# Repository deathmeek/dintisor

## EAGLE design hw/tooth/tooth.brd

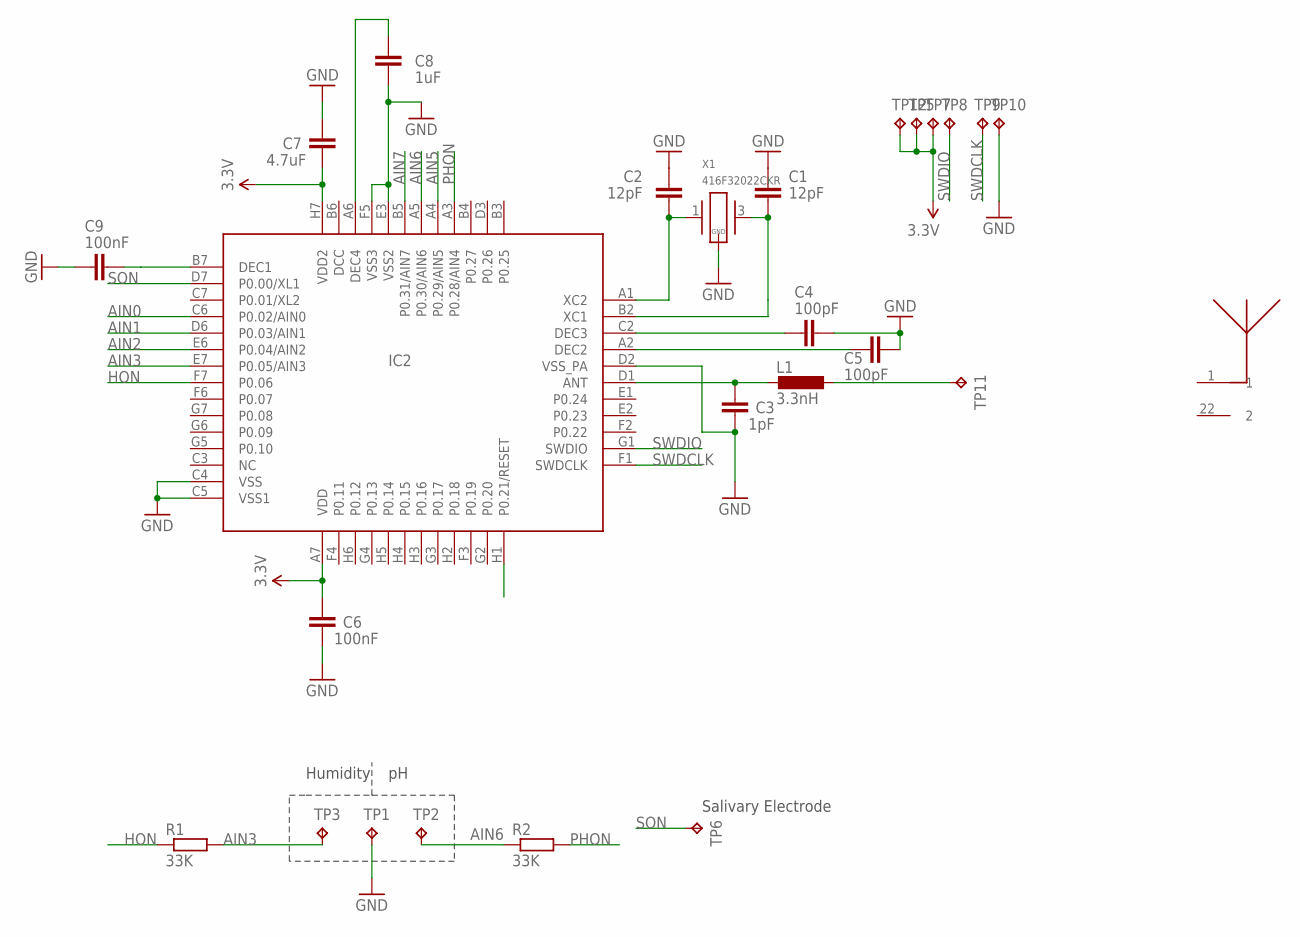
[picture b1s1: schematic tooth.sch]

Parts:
C1, C2: 12pF; C0201
C3: 1pF; C0201
C4, C5: 100pF; C0201
C6, C9: 100nF; C0201
C7: 4.7uF; C0402
C8: 1uF; C0402
IC2: NRF52832; NRF52832_WLCSP
L1: 3.3nH; L0201
R1, R2: 33K; R0201
TP1, TP2, TP3, TP11: TPTP10R; TP10R
TP5, TP6, TP7, TP8, TP9, TP10, TP12: TPTP15R; TP15R
U$1: ACA-102-T
X1: 416F32022CKR; M416

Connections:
3.3V: C6.2, C7.2, IC2.A7 (VDD), IC2.H7 (VDD2), TP5.TP, TP7.TP, TP12.TP
AIN0: IC2.C6 (P0.02/AIN0)
AIN1: IC2.D6 (P0.03/AIN1)
AIN2: IC2.E6 (P0.04/AIN2)
AIN3: IC2.E7 (P0.05/AIN3), R1.2, TP3.TP
AIN5: IC2.A4 (P0.29/AIN5)
AIN6: IC2.A5 (P0.30/AIN6), R2.1, TP2.TP
AIN7: IC2.B5 (P0.31/AIN7)
GND: C1.1, C2.1, C3.2, C4.2, C5.2, C6.1, C7.1, C8.2, C9.2, IC2.C4 (VSS), IC2.C5 (VSS1), IC2.D2 (VSS_PA), IC2.E3 (VSS2), IC2.F5 (VSS3), TP1.TP, TP10.TP, X1.2 (GND), X1.4 (GND)
HON: IC2.F7 (P0.06), R1.1
unnamed: C2.2, IC2.A1 (XC2), X1.1
unnamed: L1.1, TP11.TP
unnamed: C1.2, IC2.B2 (XC1), X1.3 (2)
unnamed: C4.1, IC2.C2 (DEC3)
unnamed: C5.1, IC2.A2 (DEC2)
unnamed: C3.1, IC2.D1 (ANT), L1.2
unnamed: C9.1, IC2.B7 (DEC1)
unnamed: C8.1, IC2.A6 (DEC4)
PHON: IC2.A3 (P0.28/AIN4), R2.2
SON: IC2.D7 (P0.00/XL1), TP6.TP
SWDCLK: IC2.F1 (SWDCLK), TP9.TP
SWDIO: IC2.G1 (SWDIO), TP8.TP

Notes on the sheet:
Humidity
Salivary Electrode

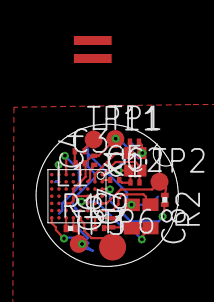
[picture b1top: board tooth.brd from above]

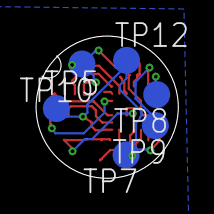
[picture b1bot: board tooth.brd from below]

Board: 2 copper layers, 7.9 x 7.9 mm, 26 parts (6 on the bottom side), 17 nets.

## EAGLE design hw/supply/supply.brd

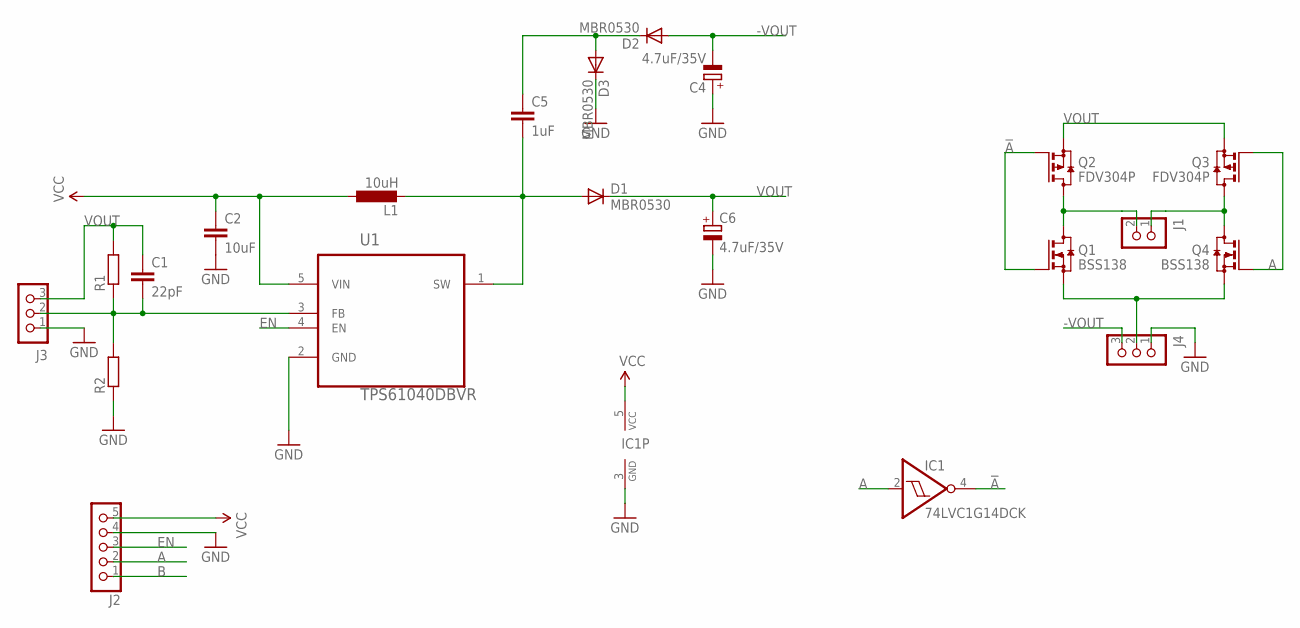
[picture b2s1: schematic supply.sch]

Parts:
C1: 22pF; C0603
C2: 10uF; C0603
C4, C6: 4.7uF/35V; 140CLH-1010
C5: 1uF; C0603
D1, D2, D3: MBR0530; SOD123
IC1: 74LVC1G14DCK; SC70-5
J1: CON_HEADER_1X02-PTH; M1X2
J2: CON_HEADER_1X05-PTH; M1X5
J3, J4: CON_HEADER_1X03-PTH; M1X3
L1: 10uH; L2825P
Q1, Q4: BSS138; SOT23
Q2, Q3: FDV304P; SOT23
R1, R2: R-EU_R0603; R0603
U1: TPS61040DBVR; SOT95P280X145-5N

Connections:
!A: IC1.4 (O), Q1.1 (G), Q2.1 (G)
-VOUT: C4.-, D2.A, J4.3
A: IC1.2 (I), J2.2, Q3.1 (G), Q4.1 (G)
B: J2.1
EN: J2.3, U1.4 (EN)
GND: C2.2, C4.+, C6.-, D3.C, IC1.3 (GND), J2.4, J3.1, J4.1, R2.1, U1.2 (GND)
unnamed: C1.2, J3.2, R1.1, R2.2, U1.3 (FB)
unnamed: C5.2, D1.A, L1.2, U1.1 (SW)
unnamed: J1.2, Q1.3 (D), Q2.3 (D)
unnamed: J1.1, Q3.3 (D), Q4.3 (D)
unnamed: C5.1, D2.C, D3.A
unnamed: J4.2, Q1.2 (S), Q4.2 (S)
VCC: C2.1, IC1.5 (VCC), J2.5, L1.1, U1.5 (VIN)
VOUT: C1.1, C6.+, D1.C, J3.3, Q2.2 (S), Q3.2 (S), R1.2

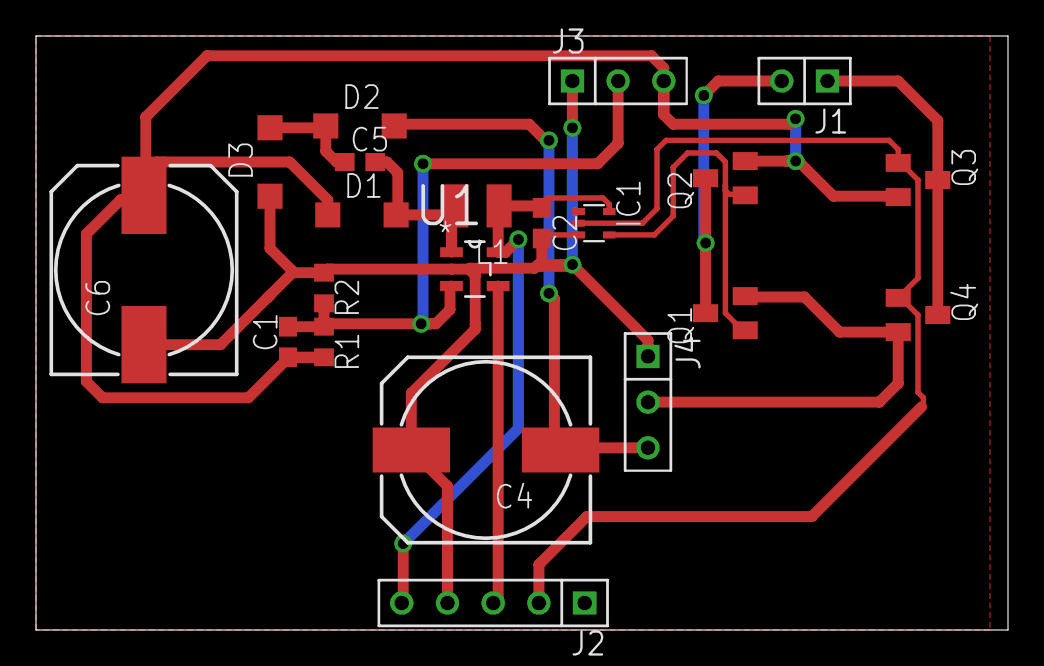
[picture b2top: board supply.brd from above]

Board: 2 copper layers, 54.0 x 33.0 mm, 21 parts (0 on the bottom side), 13 nets.

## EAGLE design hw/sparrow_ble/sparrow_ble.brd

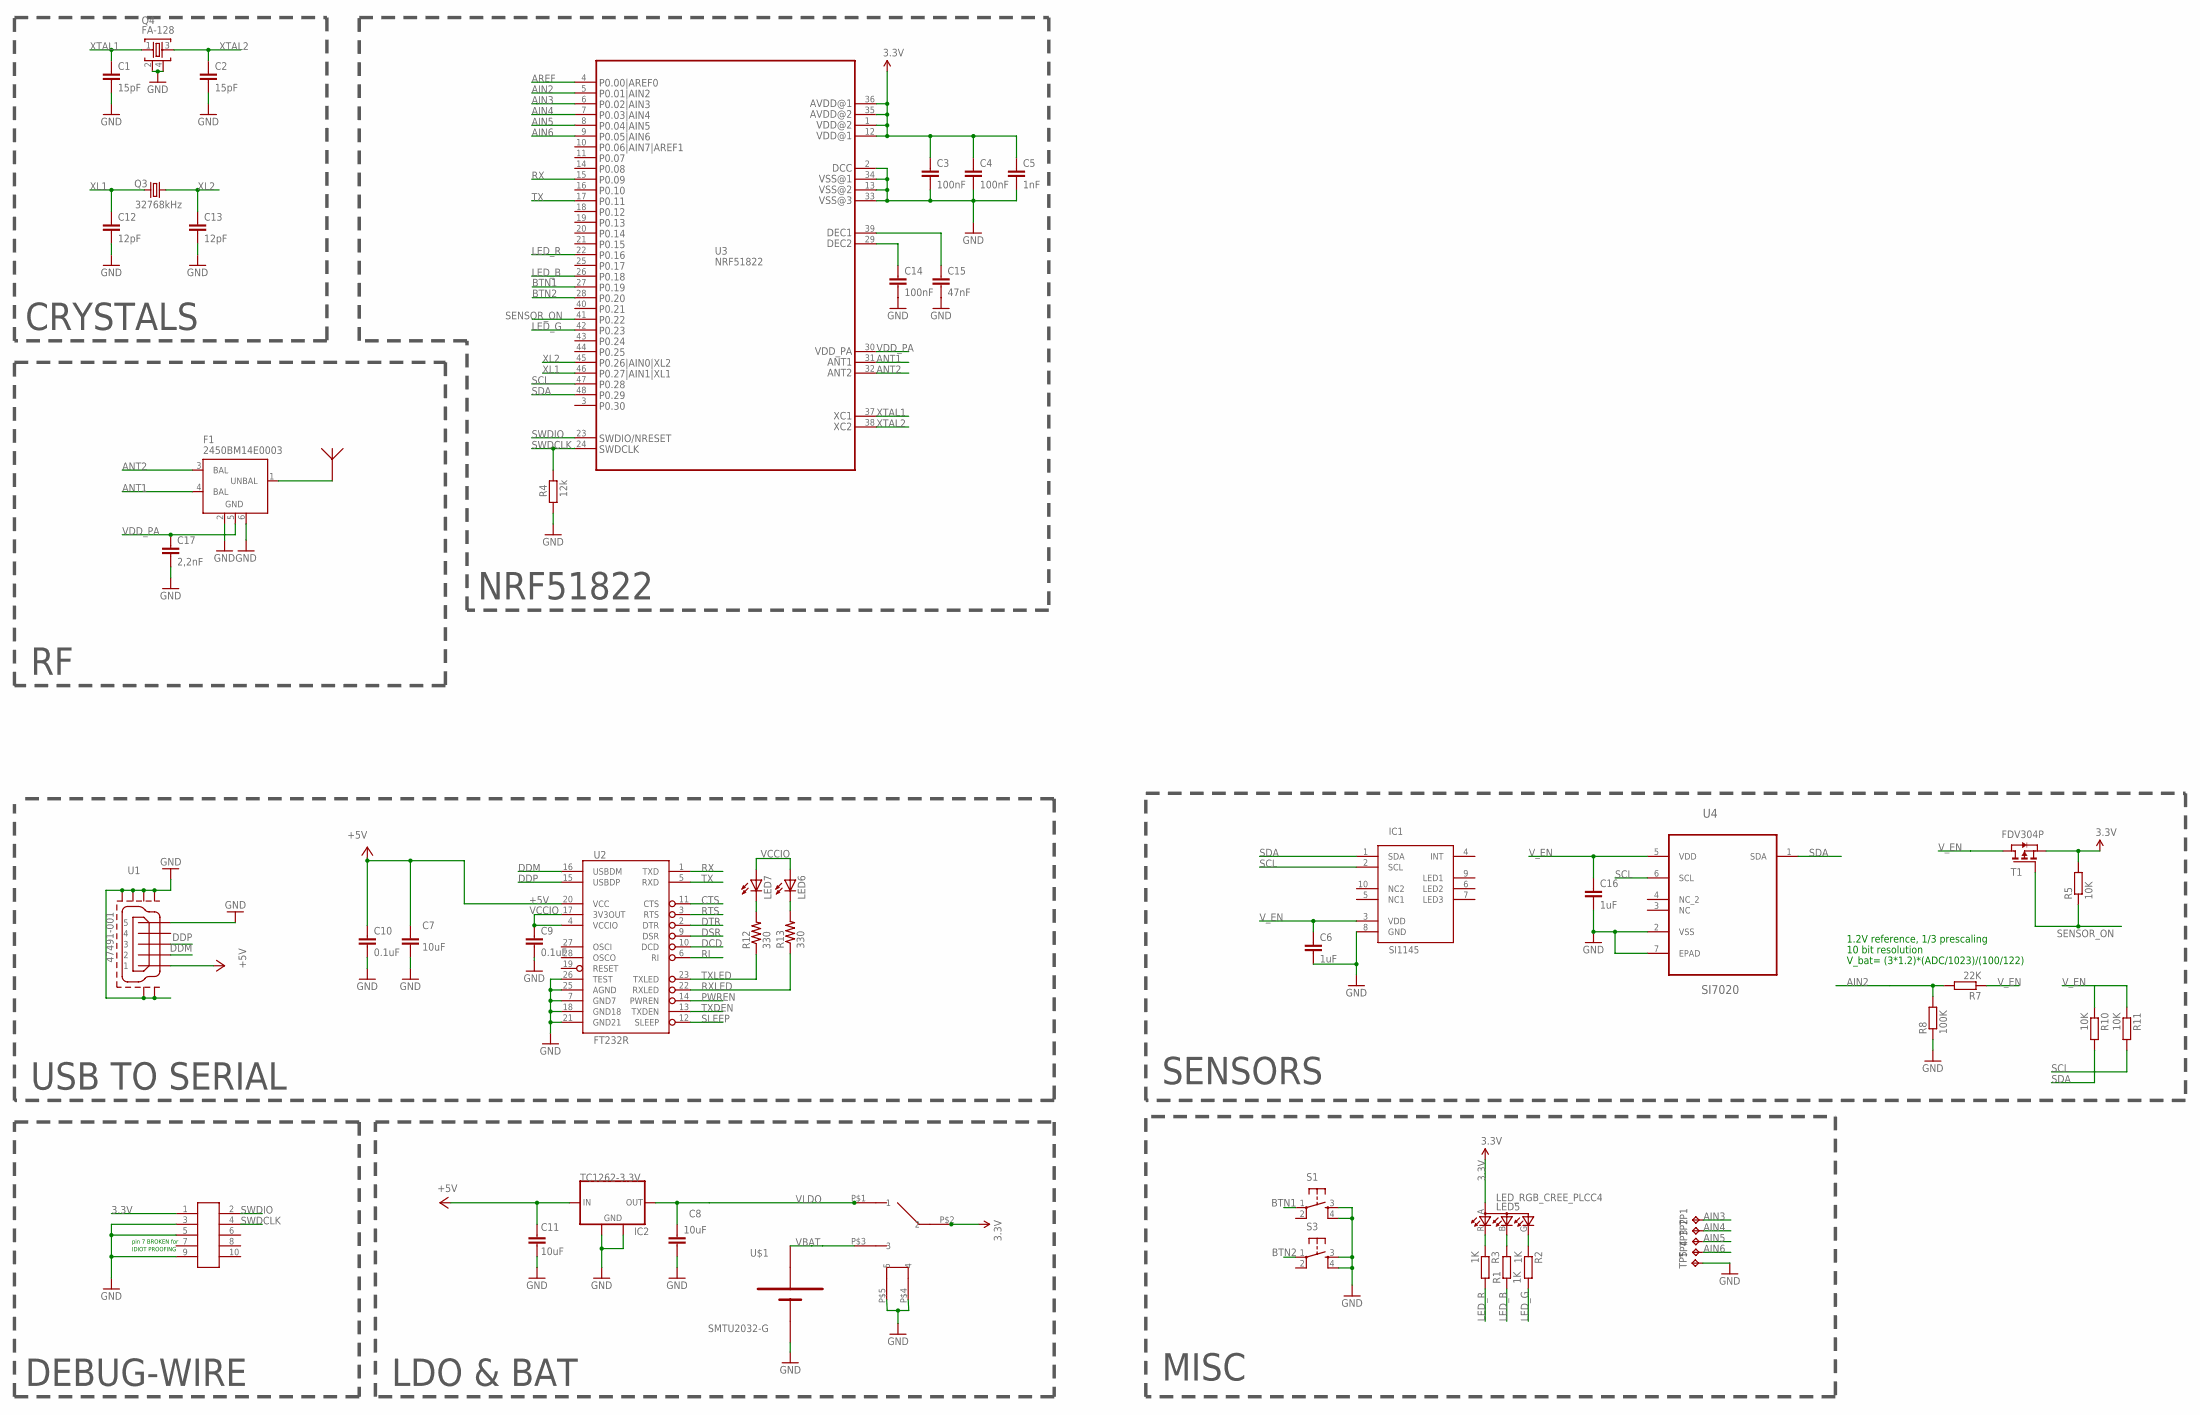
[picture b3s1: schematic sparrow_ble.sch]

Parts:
C1, C2: 15pF; C0402
C3, C4, C14: 100nF; C0402
C5: 1nF; C0402
C6, C16: 1uF; C0402
C7, C8, C11: 10uF; C0402
C9, C10: 0.1uF; 0402-CAP
C12, C13: 12pF; C0402
C15: 47nF; C0402
C17: 2,2nF; C0402
F1: 2450BM14E0003; 2450BM15A0002
IC1: SI1145; QFN10
IC2: TC1262-3.3V; SOT223
J3: SMALL_HEADER_5X2; SAMTEC_5X2
LED5: LED_RGB_CREE_PLCC4; P-LCC-4-4
LED6, LED7: LEDCHIP-LED0603; CHIP-LED0603
Q3: 32768kHz; FC-12M
Q4: FA-128
R1, R2, R3: 1K; R0402
R4: 12k; R0402
R5, R10, R11: 10K; R0402
R7: 22K; R0402
R8: 100K; R0402
R12, R13: 330; 0402-RES
S1, S3: TAC_SWITCHSMD; TACTILE-SWITCH-SMD
T1: FDV304P; SOT-23
TP1, TP2, TP3, TP4, TP5: TPTP16R; TP16R
U1: 47491-001; 47491-0001
U2: FT232R; SSOP28DB
U3: NRF51822; NRF51822-QFN48
U4: SI7020; DFN300X300X110-7N
U8: ANTENNA; ANTPACK
U$1: SMTU2032-G
U$2: SWITCH; PCM12

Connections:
3.3V: C3.1, C4.1, C5.1, J3.1, LED5.A (A2), R5.2, T1.2 (S), U3.1, U3.12, U3.35, U3.36, U$2.P$2 (2)
+5V: C7.1, C10.1, C11.1, IC2.1 (IN), U1.1, U2.20 (VCC)
AIN2: R7.2, R8.2, U3.5
AIN3: TP1.TP, U3.6
AIN4: TP2.TP, U3.7
AIN5: TP3.TP, U3.8
AIN6: TP4.TP, U3.9
ANT1: F1.4 (BAL), U3.31
ANT2: F1.3 (BAL), U3.32
AREF: U3.4
BTN1: S1.1, U3.27
BTN2: S3.1, U3.28
CTS: U2.11 (CTS)
DCD: U2.10 (DCD)
DDM: U1.2, U2.16 (USBDM)
DDP: U1.3, U2.15 (USBDP)
DSR: U2.9 (DSR)
DTR: U2.2 (DTR)
GND: C1.2, C2.2, C3.2, C4.2, C5.2, C6.2, C7.2, C8.2, C9.2, C10.2, C11.2, C12.2, C13.2, C14.2, C15.2, C16.2, C17.2, F1.2 (GND), F1.6 (GND), IC1.8 (GND), IC2.2 (GND), IC2.4 (GND), J3.3, J3.5, J3.9, Q4.2, Q4.4, R4.1, R8.1, S1.3, S1.4, S3.3, S3.4, TP5.TP, U1.5, U1.GND1, U1.GND2, U1.GND3, U1.GND4, U1.GND5, U1.GND6, U2.7 (GND7), U2.18 (GND18), U2.21 (GND21), U2.25 (AGND), U2.26 (TEST), U3.2, U3.13, U3.33, U3.34, U4.2 (VSS), U4.7 (EPAD), U$1.2, U$2.P$4 (4), U$2.P$5 (5)
LED_B: R1.1, U3.26
LED_G: R2.2, U3.42
LED_R: R3.2, U3.22
unnamed: LED5.R (CRED), R3.1
unnamed: LED5.G (CGREEN), R2.1
unnamed: C14.1, U3.29
unnamed: C15.1, U3.39
unnamed: LED7.C, R12.2
unnamed: LED6.C, R13.2
unnamed: LED5.B (CBLUE), R1.2
unnamed: F1.1 (UNBAL), U8.P$1
PWREN: U2.14 (PWREN)
RI: U2.6 (RI)
RTS: U2.3 (RTS)
RX: U2.1 (TXD), U3.15
RXLED: R13.1, U2.22 (RXLED)
SCL: IC1.2 (SCL), R11.2, U3.47, U4.6 (SCL)
SDA: IC1.1 (SDA), R10.2, U3.48, U4.1 (SDA)
SENSOR_ON: R5.1, T1.3 (G), U3.41
SLEEP: U2.12 (SLEEP)
SWDCLK: J3.4, R4.2, U3.24
SWDIO: J3.2, U3.23
TX: U2.5 (RXD), U3.17
TXDEN: U2.13 (TXDEN)
TXLED: R12.1, U2.23 (TXLED)
VBAT: U$1.1, U$2.P$3 (3)
VCCIO: C9.1, LED6.A, LED7.A, U2.4 (VCCIO), U2.17 (3V3OUT)
VDD_PA: C17.1, F1.5 (GND), U3.30
VLDO: C8.1, IC2.3 (OUT), U$2.P$1 (1)
V_EN: C6.1, C16.1, IC1.3 (VDD), R7.1, R10.1, R11.1, T1.1 (D), U4.5 (VDD)
XL1: C12.1, Q3.2, U3.46
XL2: C13.1, Q3.1, U3.45
XTAL1: C1.1, Q4.1, U3.37
XTAL2: C2.1, Q4.3, U3.38

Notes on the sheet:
pin 7 BROKEN for
IDIOT PROOFING
DEBUG-WIRE
NRF51822
CRYSTALS
1.2V reference, 1/3 prescaling
10 bit resolution
V_bat= (3*1.2)*(ADC/1023)/(100/122)
USB TO SERIAL
LDO & BAT
MISC
SENSORS

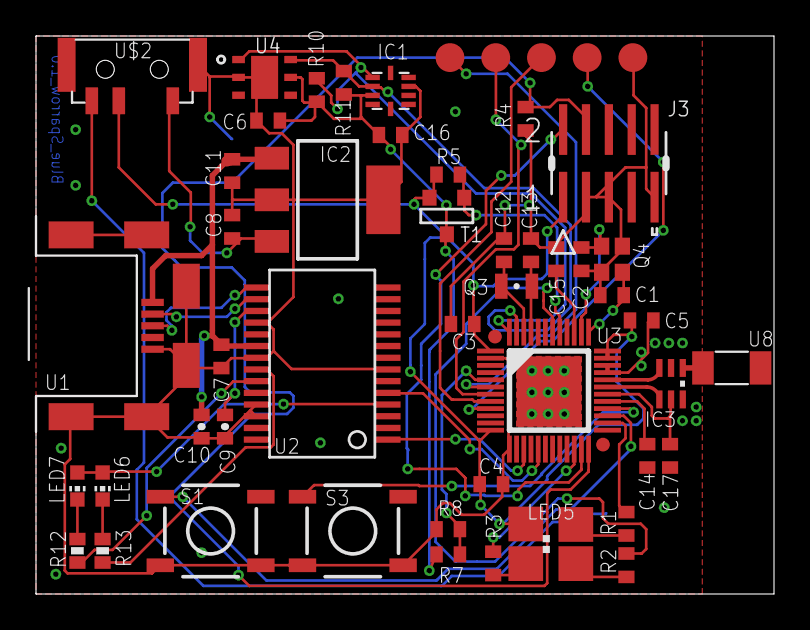
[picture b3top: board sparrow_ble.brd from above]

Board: 2 copper layers, 41.0 x 31.0 mm, 52 parts (1 on the bottom side), 43 nets.

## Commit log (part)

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2015-11-06 Add stripped down SDK v9.0.0 with S110 and HTS example
2015-11-06 Fix cross-compiling conventions
2015-11-06 Add Eclipse project files
2015-11-06 Fix Eclipse indexer paths and symbols discovery
2015-11-09 Add Eclipse launch configurations for flashing
2015-11-13 Add UART support (for debugging)
2015-11-13 Add debug output in case of error
2015-11-13 Refactor out health thermometer code
2015-11-16 Add board support for Sparrow BLE
2015-11-16 Add build support for Sparrow BLE
2015-11-16 Add Eclipse project support for Sparrow BLE
2015-11-16 Add Eclipse support for uploading bare-metal apps
2015-11-16 Add programmer ID to upload configurations
    This will allow uploading even if both programmers are connected.
2015-11-19 Add prototype schematic and board
2016-02-01 Dintișor app
2016-02-04 Fix path of softdevice upload configurations
2016-02-04 Add launch configurations for easy flash erasing
2016-02-04 Update Eclipse project settings
2016-02-04 Add analog reading of VDD value
2016-02-04 Refactor Battery Service into separate file
2016-02-09 Add custom service for sensing
2016-02-11 Add ADC readout for sensing characteristic
2016-02-11 Add new version with fixed balun
2016-02-11 Switch ADC channel to measure chip and peripheral voltage
2016-02-11 Add manual control and feedback on button 1 for peripheral voltage
2016-04-13 Updated gitignore to drop Android studio files
2016-04-15 Visual and architectural update
    Update from the basic 2-graph version.
    Now the application has multiple screens ( some of them empty at the
    moment ), an updated graph display ( a single graph which contains both
    data results ) and an updated internal architecture to address the new
    requirements.
2016-04-18 Add stimulation service skeleton
2016-04-18 Clean-up Eagle generated files
2016-04-18 Add separate UI classes for each view
2016-04-18 Add configuration for project VCS
2016-04-18 Clean used packages
2016-04-18 Add multiple MACs for Microsal device
2016-04-18 app: Fix packages
2016-04-18 hw: Update ADC design with values used on actual hardware
2016-04-19 app: Clean part of the Android Studio project/generated files
2016-04-19 app: Remove more Android Studio project files
2016-04-19 app: Refactor BLE scanning logic to remove unneeded thread
2016-04-20 fw: Fix broken build for nRF DK
2016-04-20 app: Improve BLE device scanning logic when dealing with repeat device
    The first acceptable device is selected and all other devices are ignored.
2016-04-20 app: Improve logging in BLE scan for easier searching
    The logging is now more consistent and can be filtered by the Bluetooth keyword.
2016-04-20 app: Fix null pointer when reading data but graph was not created/shown yet
2016-04-20 app: Fix off-by-one error when printing graph points
2016-04-27 fw: Add new build configuration for nRF51 Dongle
2016-04-27 fw: Improve path independence of Eclipse project files
2016-04-27 fw: Add generation of debug symbols for simpler debugging
2016-04-27 fw: Add skeleton handling of simulate characteristics change
2016-05-06 fw: Add generation of stimulation pulses
2016-05-06 fw: Add at least 100us between positive and negative pulse
    This protects the H-bridge from short circuiting.
2016-05-10 Added write characteristics
2016-05-13 hw: Reorganize hardware folder
2016-05-13 hw: Add stimulation prototype supply schematic and board
2016-05-15 fw: Add library code to project for indexing purposes
2016-05-17 Visual fix
2016-05-17 Updated UUIDs with correct value
2016-05-17 Modify code to simplify value check
    Although it seems like a large commit, the change is small, namely
    stop using the onTextChange and use onFocusChange. This greatly simplifies
    logic and improves usability
    Note that this commit is not standalone, and at this point the code should
    not compile
2016-05-17 Updated set characteristic + bugfixes
2016-05-23 Fix the advanced button
2016-05-30 fw: Add support for stimulation round
2016-05-30 fw: Add stimulation timelimit
2016-05-30 fw: Ensure initial state of pulse generation is off
2016-06-13 Fix Bluetooth writes
    Implemented a protocol that serializes all writes, and waits untill the
    write is stored on the device. This should prevent most issues with the
    Bluetooth configuration. On the offchance we need to reset the Bluetooth
    connection this commit also implements a watchdog, which is currently
    disabled.
2016-06-21 Refactored Fragment rendering code
2016-06-22 Moved ToothWatchDog to separate file
2016-06-22 Added DB that correlates devices and pacients
    Also added new views that allow you to connect to the database and
    determine if a user is already registred for that MAC
    This will set the basis for the complete data store.
2016-10-28 fw: Add measurement of pulse amplitude
2016-10-28 fw: Reorder code for consistency with declarations
2016-10-28 fw: Rename stimulate service functions for better consistency
2016-10-28 fw: Update stimulation characteristic values according to restrictions
2016-10-28 fw: Fix acceptance bad length writes
2016-10-28 hw: Add tooth hardware design
2016-10-28 hw: Add Gerber files sent to factory
2016-10-28 hw: Add cradle for code upload
2016-10-28 hw: Add holes for contact pins
2016-10-28 hw: Update tooth design for nRF52832
2016-11-17 fw: Enable parallel build
2016-11-17 fw: Silence verbose build
2016-11-17 fw: Change error code display to hex for easier matching with docs
2016-11-17 fw: Replace JLink command shortcut with fullname
2016-11-17 fw: Cleanup stuff used by HTS
2016-11-17 fw: Add reset step before programming to wake from sleep and avoid RAMCode error
2016-11-17 fw: Fix spurious errors when stimulation interval is 0 (unlimited)
2016-11-17 fw: Add flags to assembler also
2016-11-17 hw: Rename design files for tooth
2016-11-17 fw: Add bsp folder to Eclipse project
2016-11-17 hw: Add mark point for nRF chip
2016-11-23 hw: Add serial number of chip used on prototypes
2017-03-12 Update code to work on latest Android
2017-03-14 Android second screen ( with tabs )
    Further refactored the project structure
2017-03-21 Removed all references to expandable layout
2017-04-27 fw: Replace ad-hoc ADC code with ADC driver provided by nRF
2017-04-27 fw: Update Eclipse launch configurations for code upload to JLink v6.14c
2017-04-27 fw: Enable verbose compilation in Eclipse needed for indexer
2017-04-27 fw: Add initial support for building on nRF52, for PCA10040 board
2017-04-27 fw: Add support for Tooth (MEFI) based on PCA10040
2017-05-02 fw: Add ADC support for nRF52832
2017-05-02 fw: Fix missing HAL files (currently unused) for ADC driver
2017-05-02 fw: Refactor measurement API to allow more channels per module
2017-05-02 fw: Activate asserts
2017-05-02 fw: Fix unsuccessful flash programming when controller is in sleep mode
    Resets the controller before doing any other operation.
2017-05-02 fw: Add rigorous battery voltage calculation and export to other modules
2017-05-02 fw: Cleanup custom service from advertisement for consistency
2017-05-03 fw: Add measuring and reporting of humidity and pH sensors
    Heap size was reduced for Sparrow BLE because of link errors caused by
    insufficient memory. Dynamic memory is not used in the user code so this
    should be totally safe.
2017-05-03 fw: Fix missing error check for ADC channel initialization
2017-05-03 fw: Cleanup measuring of stimulation voltage
2017-05-03 fw: Fix consistency of voltage divider calculation as an inverse gain
2017-05-03 fw: Fix Eclipse indexer issues caused by new version of SDK
    Take note, the build output parser gets especially confused by commands
    with double quotes (") in them and doesn't parse symbols defined on the
    command line.
2017-06-23 hw: Add new, smaller board revision
2017-06-28 hw: Clean-up design files
2017-06-29 fw: Fix possible redefinition of NRF_LOG_LEVEL at module level
2017-06-29 fw: Remove calculation of irrelevant sensor resistance
2017-06-29 fw: Add logging for the sense module
2017-06-29 fw: Tune BLE advertising intervals and timeouts for continuous operation
    Fast advertising last a short time, but offers better interactivity.
    Slow advertising doesn't end, but uses the longest supported advertising
    interval for low energy consumption (with the worse interactivity).
2017-06-29 fw: Fix stimulation mode for Tooth board (and some other boards)
    Tooth has a single electrode, while the other boards use 2 electrodes
    for polarity reversal. The dual electrode boards have their electodes
    connected on different pins, which is also fixed now.
2017-06-29 fw: Fix timer driver errors on starting a previously used timer
2017-06-29 fw: Reduce timer driver errors on double stopping a timer
    The errors are not fixed completely because of synchronization issues
    between BLE event handler context and timer interrupt context.
2017-06-29 fw: Add scheduler to run events in main thread for synchronization
    Without the scheduler events received in SoftDevice context are
    hard/impossible to synchronize correctly with other code.
2017-06-30 fw: Fix multiple synchronization issues with pulse timer
    Reconfiguration is now only supported at the end of a pulse train and
    the train timer is now updated appropriately. Reconfiguration in other
    moments was mostly broken.
    Stopping was refactored in order to eliminate the extra pulse added to
    the pulse train in the previous implementation.
    Critical regions were added to ensure correct operation when functions
2017-06-30 fw: Add PPI channel for stopping the pulse timer exactly
    A related change is that the round timer is more accurate now, with
    interrupt latencies being removed from the measured time interval.
2017-07-05 fw: Refactor round timer count to make it independent of the pulse timer
2017-07-05 fw: Refactor active timer code for better modularization
    As a side effect the code is also concurrency safe.
2017-07-05 fw: Cleanup stimulation module naming convention
2017-07-05 fw: Cleanup logging for stimulation module
2017-07-05 fw: Move BLE connection parameters to Connection Parameters module
    Apple doesn't honor the PPCP and from empirical tests is seems that
    Android is also ignoring it. Setting the PPCP seems irrelevant. The
    Connection Parameters module can instead negotiate the desired
    parameters.
2017-07-06 fw: Update connection parameters to maximum values
    The maximum is dictated by interaction with Apple devices as stated in
    their Bluetooth design guidelines.
2017-07-06 fw: Optimize connection parameters negotiation intervals
    The connection parameters will now be negotiated as soon as possible.
2017-07-06 fw: Remove unreachable switch branch
    The device is configured to never go idle, as the Tooth has no way of
    waking up.
2017-07-06 fw: Cleanup advertising and connection parameters
2017-07-07 sw: Patch to work
2017-07-07 sw: Fix byte order and add distributed apk
2017-07-26 sw: Fix stimulation control
2017-07-27 sw: Add listing of device name
2017-07-27 sw: Fix field inversion and unfiltered devices in lookup view
2017-07-27 sw: Change behavior to connect to selected device
2017-07-27 sw: Fix V and d display, and cleanup ToothSettings layout
2017-07-27 sw: Fix Voltage filed and cleanup tooth settings UI some more
2017-07-27 sw: Remove device filtering based on MAC as it's not needed anymore
2017-07-27 sw: Add mark for inactive devices
2017-07-27 sw: Refactor Tooth API slightly
2017-07-31 sw: Add data logging on device
2017-07-31 sw: Hack it to show newly created files over USB
2017-08-01 sw: Change log format to CSV, importable in at least LibreOffice
2017-08-01 sw: Add UI feedback for status of stimulation
2017-08-01 sw: Improve robustness on disconnection and add automatic reconnection
2017-08-01 sw: Fix UI bug of not updating settings when changing fields
2017-08-01 sw: Add logging of stimulation operations
2017-08-01 sw: Improve robustness on disconnects

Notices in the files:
parts and their libraries:
SparkFun-Electromechanical: Licensing: Creative Commons ShareAlike 4.0 International - https://creativecommons.org/licenses/by-sa/4.0
